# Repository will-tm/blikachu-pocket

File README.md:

<div align="center">

# BLikachu Pocket

**A Game Boy, NES and SNES handheld inside a Pocket Pikachu: a replacement BL618 board and Zephyr firmware for the
Nintendo MPG-001 shell.**

**[Hardware](#hardware) · [Build and flash](#build-and-flash) · [Add games](#add-games) · [Controls](#controls) · [Firmware docs](firmware/README.md)**

</div>

## New insides, same shell

- **Three systems:** GB and GBC (Gambatte), NES (FCEUmm) and SNES (Snes9x2005), picked from the ROM's header and
  extension.
- **Saves:** save states, cartridge battery RAM and RTC data, kept across firmware updates.
- **Wi-Fi:** a web UI to upload and delete ROMs, play remotely and update the firmware over the air.
- **USB:** DFU firmware updates, a shell, and ROM and save uploads without Wi-Fi.

## How it works

<p align="center">
  <picture>
    <source media="(prefers-color-scheme: dark)" srcset="assets/overview-dark.svg">
    <img alt="Inside the shell, a BL618 running Zephyr at 480 MHz loads one libretro core at a time: Gambatte for GB and GBC, FCEUmm for NES or Snes9x2005 for SNES. Its 4 MiB of PSRAM is split into 512 KiB of buffers and a 3.5 MiB core and update workspace. The buttons, IMU and power circuit feed it; it drives the ST7789V LCD and the buzzer. A 64 MiB quad SPI flash holds 8 MiB of firmware, an 8 MiB LittleFS volume for settings, saves and the ROM catalogue, and 48 MiB of contiguous, memory-mapped ROMs. A browser reaches the web UI over Wi-Fi, and a computer connects over high-speed USB." src="assets/overview-light.svg">
  </picture>
</p>

## Hardware

| Part    | Detail                                                             |
| ------- | ------------------------------------------------------------------ |
| SoC     | Bouffalo Lab BL618 RISC-V, 4 MiB PSRAM, CPU overclocked to 480 MHz |
| Flash   | W25Q512JV, 64 MiB QSPI                                             |
| Display | ST7789V SPI colour LCD, 240×216 visible                            |
| Input   | D-pad and four buttons                                             |
| Sound   | PWM buzzer                                                         |
| Motion  | LSM6DSV16X IMU                                                     |
| Power   | MCP73871 Li-ion charger, battery measurement, GPIO power latch     |
| Radio   | Wi-Fi                                                              |
| USB     | High speed: CDC shell and DFU                                      |

Open [the KiCad project](hardware/blikachu-pocket.kicad_pro) in KiCad 10.

## Build and flash

You need Python 3, CMake, Ninja, [Zephyr SDK](https://github.com/zephyrproject-rtos/sdk-ng/releases) 1.0.1 with the
RISC-V toolchain, and `dfu-util`. On macOS:

```sh
brew install cmake ninja dtc dfu-util
cd firmware
./build.sh
```

**First flash:** hold BOOT while resetting, release it, then pass the serial port that appears:

```sh
FLASH_PORT=/dev/cu.usbmodemXXXXX ./build.sh flash
```

**Updates:** with the firmware running, no buttons needed:

```sh
./build.sh flash
```

Keep power connected until the board reboots: `Download done` means the transfer has finished, not the installation.

### Recovery

An interrupted or broken install is recovered the same way as the first flash: BOOT, reset, then `./build.sh flash`
with `FLASH_PORT`. Details: [firmware documentation](firmware/README.md#firmware-updates).

## Add games

Upload your own `.gb`, `.gbc`, `.nes`, `.sfc` or `.smc` files.

**Over Wi-Fi:** add a network from the USB shell, then open the board's IP address in a browser:

```text
wifi_cred add <ssid> <passphrase>
wifi_cred connect
```

**Over USB:** from the `firmware` directory. This also sends libretro save files.

```sh
source .venv/bin/activate
python tools/usb_upload.py --port /dev/cu.usbmodemXXXXX game.gbc
```

SNES support covers ordinary LoROM and HiROM cartridges; enhancement-chip games are rejected.

## Controls

| Buttons               | Action            |
| --------------------- | ----------------- |
| SELECT + START        | Quit to the menu  |
| SELECT + B            | Save state        |
| SELECT + A            | Restore state     |
| SELECT + UP / DOWN    | Volume            |
| SELECT + LEFT / RIGHT | Brightness        |
| Hold START            | Request power-off |

On SNES, A and B act as B and Y, SELECT + A / B as A and X, and SELECT + LEFT / RIGHT as L and R. Save states and
brightness move to the shell. Remote play exposes all twelve SNES buttons.

## Development

- [Firmware documentation](firmware/README.md): cores, storage, updates and the shell.
- [Firmware development notes](firmware/CLAUDE.md): pin assignments, scheduling and memory constraints, Zephyr
  patches.

GitHub Actions builds the firmware and renders the PCB in 3D on hardware changes. The render above is refreshed on
pushes to `main`; pull requests get a preview artifact.

## Disclaimers

BLikachu Pocket is provided **as is, without any warranty**: you modify your device at your own risk.

- It is an independent hardware and firmware project, not affiliated with or endorsed by Nintendo. Nintendo, Game Boy,
  Pokémon and Pikachu are trademarks of their respective owners.
- No games are included.
- The emulator cores keep their own licenses, in their dependency repositories. Snes9x's license includes
  non-commercial distribution restrictions.

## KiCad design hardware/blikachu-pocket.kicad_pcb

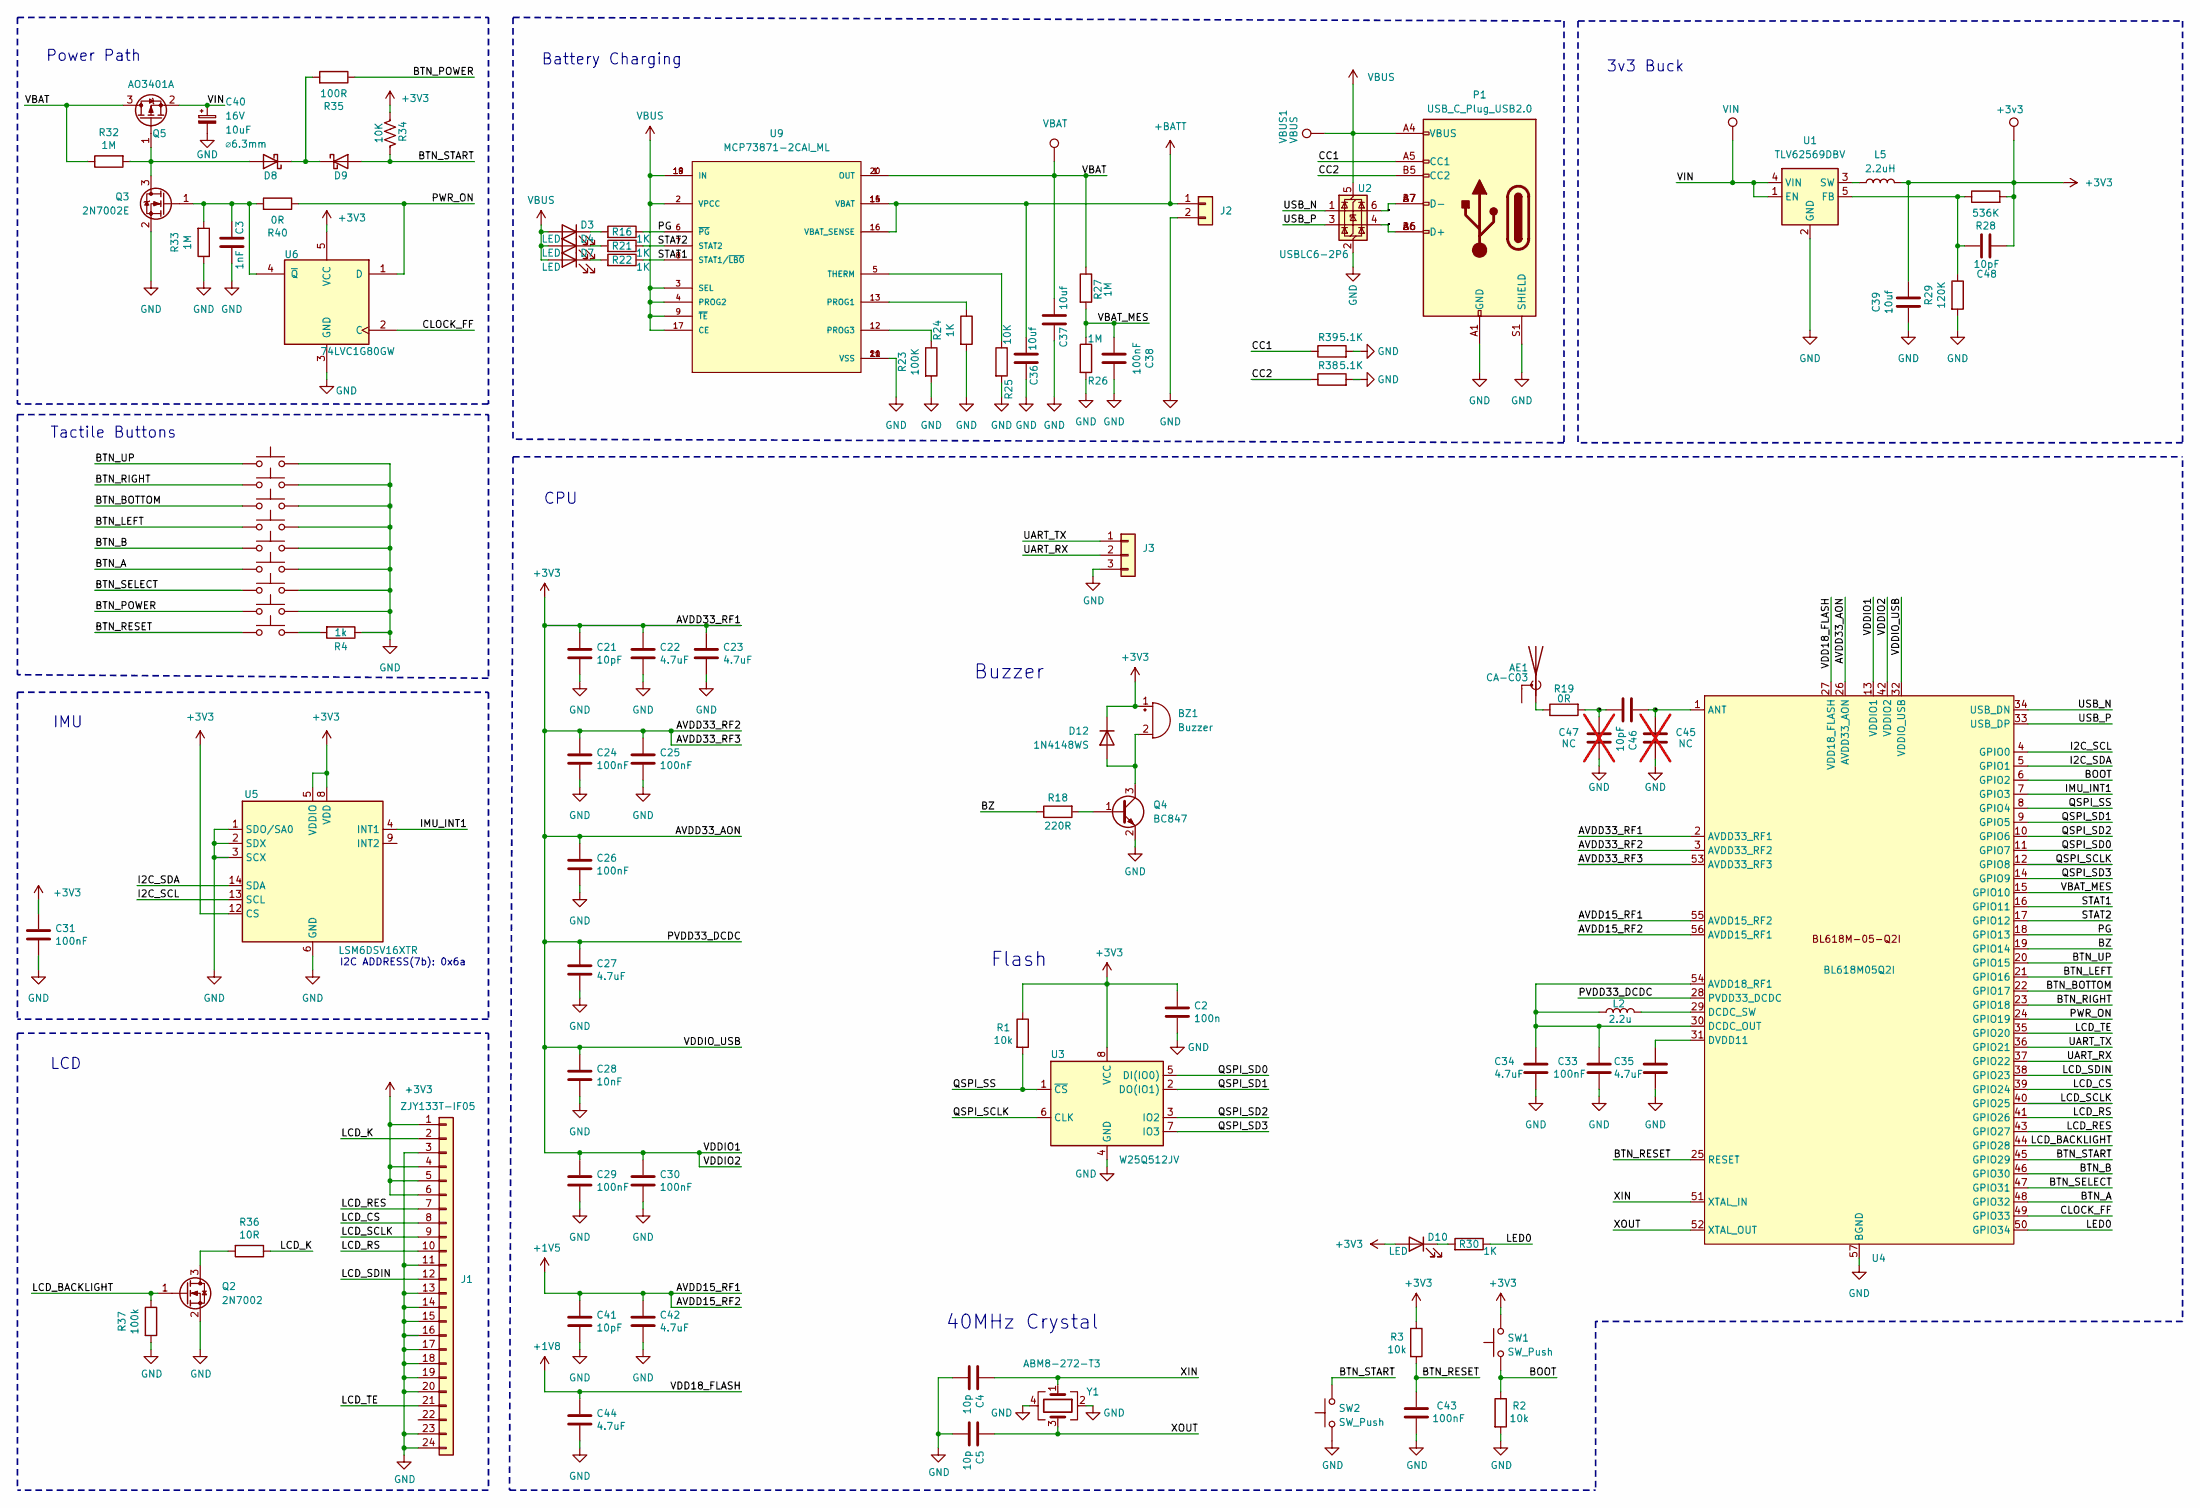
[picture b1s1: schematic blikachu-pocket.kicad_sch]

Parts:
+3v3: +3v3; TestPoint_Pad_D1.0mm
A0: ESPKACHU-PAD
AE1: CA-C03
B0: ESPKACHU-PAD
BZ1: Buzzer; CUI_CSS-0575A-SMT
C2: 100n; C_0402_1005Metric
C3: 1nF; C_0402_1005Metric
C4, C5: 10p; C_0402_1005Metric
C21, C41, C46, C48: 10pF; C_0402_1005Metric
C22, C23, C27, C34, C35, C42, C44: 4.7uF; C_0402_1005Metric
C24, C25, C26, C29, C30, C31, C33, C38, C43: 100nF; C_0402_1005Metric
C28: 10nF; C_0402_1005Metric
C36, C37: 10uf; C_0805_2012Metric
C39: 10uf; C_1206_3216Metric_Pad1.33x1.80mm_HandSolder
C40: 865080443007; C_1206_3216Metric_Pad1.33x1.80mm_HandSolder; Voltage 16V; Part Number 865080443007
C45, C47: NC; C_0402_1005Metric; not fitted
D3, D4, D7, D10: LED; LED_0603_1608Metric
D8, D9: D_Schottky; D_0603_1608Metric_Pad1.05x0.95mm_HandSolder
D12: 1N4148WS; D_SOD-323_HandSoldering
DOWN0: ESPKACHU-PAD
J1: ZJY133T-IF05; Hirose_FH12-24S-0.5SH_1x24-1MP_P0.50mm_Horizontal
J2: Conn_01x02; PinHeader_1x02_P2.00mm_Vertical
J3: Conn_01x03; PinHeader_1x03_P2.00mm_Vertical
L2: 2.2u; L_pol_2016
L5: 2.2uH; L_Changjiang_FTC201607S
LEFT0: ESPKACHU-PAD
P1: USB_C_Plug_USB2.0; USB_C_Receptacle_GCT_USB4105-xx-A_16P_TopMnt_Horizontal
Q2: 2N7002; SOT-23
Q3: 2N7002E; SOT-23
Q4: BC847; SOT-23
Q5: AO3401A; SOT-23
R1, R2, R3: 10k; R_0402_1005Metric
R4: 1k; R_0402_1005Metric
R16, R21, R22, R24, R30: 1K; R_0402_1005Metric
R18: 220R; R_0402_1005Metric
R19, R40: 0R; R_0402_1005Metric
R23: 100K; R_0402_1005Metric
R25: 10K; R_0402_1005Metric
R26, R27, R32, R33: 1M; R_0402_1005Metric
R28: 536K; R_0402_1005Metric
R29: 120K; R_0402_1005Metric
R34: 10K; R_0402_1005Metric; Tolerance 1%
R35: 100R; R_0402_1005Metric
R36: 10R; R_0805_2012Metric
R37: 100k; R_0402_1005Metric
R38, R39: 5.1K; R_0402_1005Metric; MPN RC0603FR-072K2L; Digi-Key_PN 311-2.20KHRCT-ND
RIGHT0: ESPKACHU-PAD
SELECT0: ESPKACHU-PAD
START0, START1: ESPKACHU-PAD
SW1, SW2: SW_Push; TS-A001A
U1: TLV62569DBV; SOT-23-5
U2: USBLC6-2P6; SOT-666
U3: W25Q512JV; SOIC-8_5.3x6.2mm_P1.27mm
U4: BL618M05Q2I; QFN-56_EP_7x7_Pitch0.4mm
U5: LSM6DSV16XTR; LGA-14_3x2.5mm_P0.5mm_LayoutBorder3x4y
U6: 74LVC1G80GW; SOT-353_SC-70-5
U9: MCP73871-2CAI_ML; QFN-20-1EP_4x4mm_P0.5mm_EP2.5x2.5mm_ThermalVias; PARTREV D
UP0: ESPKACHU-PAD
VBAT1: VBAT; TestPoint_Pad_D1.0mm
VBUS1: VBUS; TestPoint_Pad_D1.0mm
VIN1: VIN; TestPoint_Pad_D1.0mm
Y1: ABM8-272-T3; Crystal_SMD_3225-4Pin_3.2x2.5mm

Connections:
+1V5: C41.1, C42.1, U4.55 (AVDD15_RF2), U4.56 (AVDD15_RF1)
+1V8: C44.1, U4.27 (VDD18_FLASH)
+3V3: +3v3.1 (1_1), BZ1.1 (-), C2.1, C21.1, C22.1, C23.1, C24.1, C25.1, C26.1, C27.1, C28.1, C29.1, C30.1, C31.1, C39.2, C48.1, D10.2 (A), D12.2 (K), J1.1, J1.4, J1.5, J1.6, L5.2, R1.1, R3.1, R28.2, R34.2, SW1.2, U3.8 (VCC), U4.2 (AVDD33_RF1), U4.3 (AVDD33_RF2), U4.13 (VDDIO1), U4.26 (AVDD33_AON), U4.28 (PVDD33_DCDC), U4.32 (VDDIO_USB), U4.42 (VDDIO2), U4.53 (AVDD33_RF3), U5.5 (VDDIO), U5.8 (VDD), U5.12 (CS), U6.5 (VCC)
+BATT: C36.2, J2.1, U9.14 (VBAT), U9.15 (VBAT), U9.16 (VBAT_SENSE)
/ANT_PATH1: C45.1, C46.1, U4.1 (ANT)
/ANT_PATH2: C46.2, C47.1, R19.2
/BOOT: R2.1, SW1.1, U4.6 (GPIO2)
/BTN_A: A0.1, U4.48 (GPIO32)
/BTN_B: B0.1, U4.46 (GPIO30)
/BTN_BOTTOM: DOWN0.1, U4.22 (GPIO17)
/BTN_LEFT: LEFT0.1, U4.21 (GPIO16)
/BTN_POWER: R35.1, START0.1
/BTN_RESET: C43.1, R3.2, START1.1, U4.25 (RESET)
/BTN_RIGHT: RIGHT0.1, U4.23 (GPIO18)
/BTN_SELECT: SELECT0.1, U4.47 (GPIO31)
/BTN_START: D9.2 (A), R34.1, SW2.2, U4.45 (GPIO29)
/BTN_UP: U4.20 (GPIO15), UP0.1
/BZ: R18.1, U4.19 (GPIO14)
/CC1: P1.A5 (CC1), R39.1
/CC2: P1.B5 (CC2), R38.1
/CLOCK_FF: U4.49 (GPIO33), U6.2 (C)
/I2C_SCL: U4.4 (GPIO0), U5.13 (SCL)
/I2C_SDA: U4.5 (GPIO1), U5.14 (SDA)
/IMU_INT1: U4.7 (GPIO3), U5.4 (INT1)
/LCD_BACKLIGHT: Q2.1 (G), R37.1, U4.44 (GPIO28)
/LCD_CS: J1.8, U4.39 (GPIO24)
/LCD_K: J1.2, R36.1
/LCD_RES: J1.7, U4.43 (GPIO27)
/LCD_RS: J1.10, U4.41 (GPIO26)
/LCD_SCLK: J1.9, U4.40 (GPIO25)
/LCD_SDIN: J1.12, U4.38 (GPIO23)
/LCD_TE: J1.21, U4.35 (GPIO20)
/LED0: R30.1, U4.50 (GPIO34)
/PG: R16.1, U4.18 (GPIO13), U9.6 (~PG)
/PWR_ON: R40.1, U4.24 (GPIO19), U6.1 (D)
/QSPI_SCLK: U3.6 (CLK), U4.12 (GPIO8)
/QSPI_SD0: U3.5 (DI(IO0)), U4.11 (GPIO7)
/QSPI_SD1: U3.2 (DO(IO1)), U4.9 (GPIO5)
/QSPI_SD2: U3.3 (IO2), U4.10 (GPIO6)
/QSPI_SD3: U3.7 (IO3), U4.14 (GPIO9)
/QSPI_SS: R1.2, U3.1 (~CS), U4.8 (GPIO4)
/STAT1: R22.1, U4.16 (GPIO11), U9.8 (STAT1/~LBO)
/STAT2: R21.1, U4.17 (GPIO12), U9.7 (STAT2)
/UART_RX: J3.2, U4.37 (GPIO22)
/UART_TX: J3.1, U4.36 (GPIO21)
/USB_CON_N: P1.A7 (D-), P1.B7 (D-), U2.6 (I/O1)
/USB_CON_P: P1.A6 (D+), P1.B6 (D+), U2.4 (I/O2)
/USB_N: U2.1 (I/O1), U4.34 (USB_DN)
/USB_P: U2.3 (I/O2), U4.33 (USB_DP)
/VBAT: C37.2, Q5.3 (D), R27.1, R32.1, U9.1 (OUT), U9.20 (OUT), VBAT1.1 (1_1)
/VBAT_MES: C38.2, R26.1, R27.2, U4.15 (GPIO10)
/VIN: C40.1, Q5.2 (S), U1.1 (EN), U1.4 (VIN), VIN1.1 (1_1)
/XIN: C4.1, U4.51 (XTAL_IN), Y1.1
/XOUT: C5.1, U4.52 (XTAL_OUT), Y1.3
GND: A0.2, B0.2, C2.2, C3.1, C4.2, C5.2, C21.2, C22.2, C23.2, C24.2, C25.2, C26.2, C27.2, C28.2, C29.2, C30.2, C31.2, C33.2, C34.2, C35.2, C36.1, C37.1, C38.1, C39.1, C40.2, C41.2, C42.2, C43.2, C44.2, C45.2, C47.2, DOWN0.2, J1.3, J1.11, J1.13, J1.14, J1.15, J1.16, J1.17, J1.18, J1.19, J1.20, J1.23, J1.24, J2.2, J3.3, LEFT0.2, P1.A1 (GND), P1.A12 (GND), P1.B1 (GND), P1.B12 (GND), P1.S1 (SHIELD), Q2.2 (S), Q3.2 (S), Q4.2 (E), R2.2, R4.1, R23.2, R24.2, R25.2, R26.2, R29.2, R33.1, R37.2, R38.2, R39.2, RIGHT0.2, SELECT0.2, START0.2, SW2.1, U1.2 (GND), U2.2 (GND), U3.4 (GND), U4.57 (BGND), U5.1 (SDO/SA0), U5.2 (SDX), U5.3 (SCX), U5.6 (GND), U5.7 (GND), U6.3 (GND), U9.10 (VSS), U9.11 (VSS), U9.21 (VSS), UP0.2, Y1.2, Y1.4
unnamed: AE1.1 (A_1), R19.1
unnamed: BZ1.2 (+), D12.1 (A), Q4.3 (C)
unnamed: D3.1 (K), R16.2
unnamed: D4.1 (K), R21.2
unnamed: D7.1 (K), R22.2
unnamed: D8.2 (A), Q3.3 (D), Q5.1 (G), R32.2
unnamed: D8.1 (K), D9.1 (K), R35.2
unnamed: D10.1 (K), R30.2
unnamed: Q2.3 (D), R36.2
unnamed: C3.2, Q3.1 (G), R33.2, R40.2, U6.4 (~Q)
unnamed: Q4.1 (B), R18.2
unnamed: R4.2, START1.2
unnamed: C48.2, R28.1, R29.1, U1.5 (FB)
unnamed: L5.1, U1.3 (SW)
unnamed: C33.1, C34.1, L2.1, U4.30 (DCDC_OUT), U4.54 (AVDD18_RF1)
unnamed: L2.2, U4.29 (DCDC_SW)
unnamed: C35.1, U4.31 (DVDD11)
unnamed: R24.1, U9.13 (PROG1)
unnamed: R23.1, U9.12 (PROG3)
unnamed: R25.1, U9.5 (THERM)
VBUS: D3.2 (A), D4.2 (A), D7.2 (A), P1.A4 (VBUS), P1.A9 (VBUS), P1.B4 (VBUS), P1.B9 (VBUS), U2.5 (VBUS), U9.2 (VPCC), U9.3 (SEL), U9.4 (PROG2), U9.9 (~TE), U9.17 (CE), U9.18 (IN), U9.19 (IN), VBUS1.1 (1_1)

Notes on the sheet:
Tactile Buttons
Battery Charging
3v3 Buck
LCD
Power Path
CPU
I2C ADDRESS(7b): 0x6a
40MHz Crystal
Buzzer
Flash
IMU

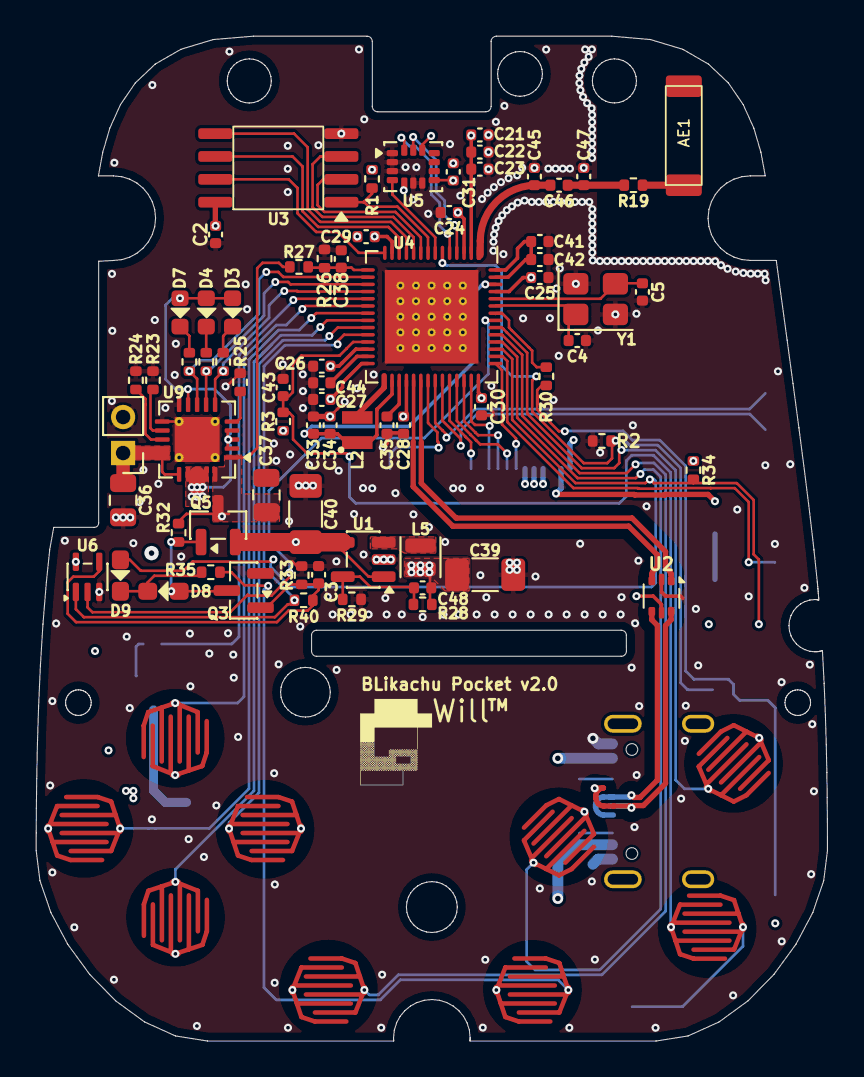
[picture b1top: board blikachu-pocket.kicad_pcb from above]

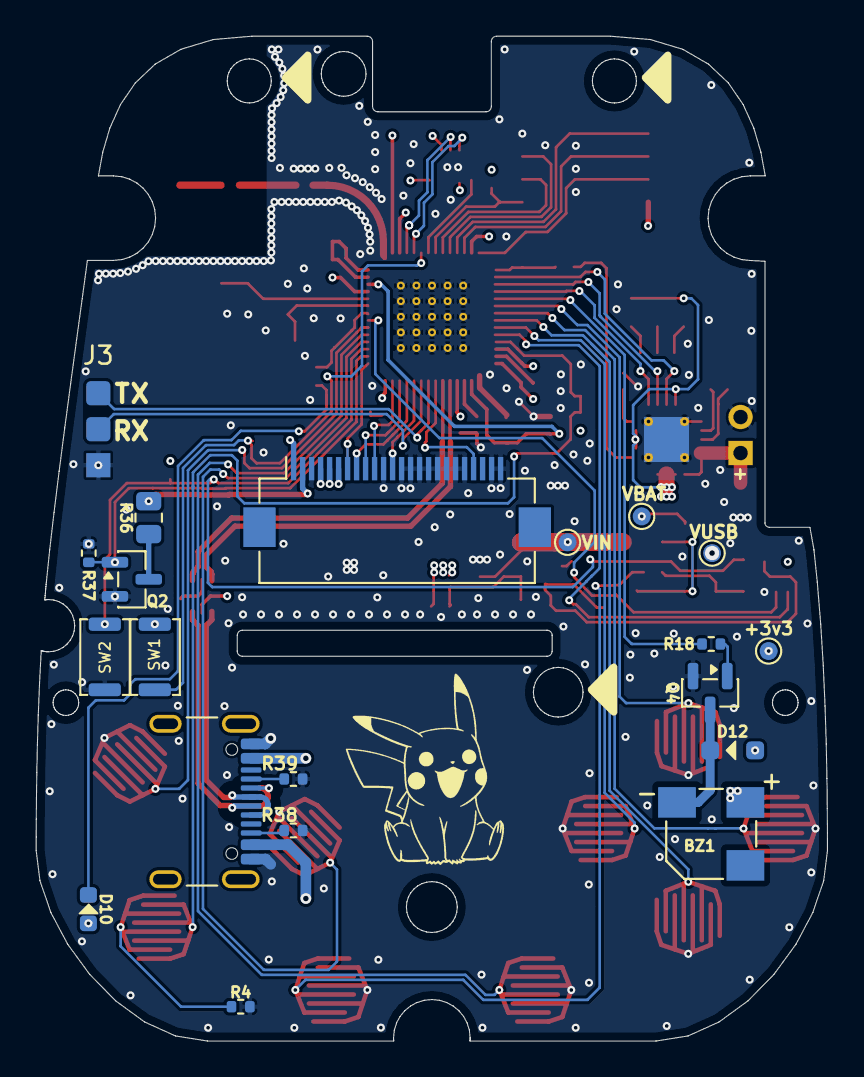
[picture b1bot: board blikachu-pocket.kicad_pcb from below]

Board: 4 copper layers, 44.0 x 55.8 mm, 99 parts (20 on the bottom side), 76 nets.

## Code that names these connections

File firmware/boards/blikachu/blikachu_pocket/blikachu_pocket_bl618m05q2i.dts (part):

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 *
 * Pin map (from hardware/ PCB netlist — pads are ground truth,
 * the schematic is partly an Eagle import):
 *   I2C0 (LSM6DSV16X IMU, INT1=GPIO3):
 *     SCL=GPIO0  SDA=GPIO1
 *   BOOT button (SW1, to +3V3 — BootROM entry, not an input key):
 *     GPIO2
 *   QSPI flash on SF2 pad set (external — BL618M05 has no internal
 *   die): W25Q512JV 64 MB (U3).
 *     CS=GPIO4 D1=GPIO5 D2=GPIO6 D0=GPIO7 CLK=GPIO8 D3=GPIO9
 *   Battery measurement: VBAT_MES=GPIO10 (VBAT/2, ADC CH7)
 *   Charger status (MCP73871, open-drain active-low):
 *     STAT1=GPIO11  STAT2=GPIO12  PG=GPIO13
 *   Magnetic buzzer (BZ1 on +3V3 via Q4 BC847, D12 flyback):
 *     GPIO14 (PWM0 CH2P)
 *   D-pad / buttons (active-low, internal pull-up):
 *     UP=GPIO15  LEFT=GPIO16  DOWN=GPIO17  RIGHT=GPIO18
 *     START=GPIO29  B=GPIO30  SELECT=GPIO31  A=GPIO32
 *   Power latch (74LVC1G80 ~Q -> Q3 NMOS -> Q5 PMOS, VBAT->VIN):
 *     D=GPIO19 (/PWR_ON)  CP=GPIO33 (/CLOCK_FF)
 *     R40 (0R) ties D to ~Q: a toggle flip-flop, each CP rising edge
 *     flips power. ~Q high = held. GPIO19 is input-only (reads ~Q).
 *     Power button pulls Q5's gate via D8 (and reads as START via D9).
 *   ST7789V SPI 240x240 (ZJY133T-IF05 FPC, write-only):
 *     MOSI=GPIO23  CS=GPIO24  SCLK=GPIO25  DC(RS)=GPIO26  RST=GPIO27
 *     TE=GPIO20  Backlight=GPIO28 (Q2 low-side, PWM0 CH0P)
 *   UART0 console/shell (J3 header + CKLink adapter):
 *     TX=GPIO21  RX=GPIO22  (BootROM download pins too)
 *   USB-C: native USB HS PHY (dedicated pins, via USBLC6 ESD) —
 *     CDC ACM shell via the bl61x UDC (patches/0003).
 *   LED0=GPIO34
 *
 * GPIO numbering: gpio0 covers GPIO0-31, gpio1 covers GPIO32-34
 * (pins 0-2).
 *
 * Flash layout (64 MB W25Q512JV, 4-byte addresses):
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
	zephyr,user {
		/* ST7789V tear-effect output. */
		te-gpios = <&gpio0 20 GPIO_ACTIVE_HIGH>;
		/* Backlight moved off PWM0 (single global period shared
		 * with the buzzer — every note retuned it): timer0
		 * soft-PWM drives the pin as plain GPIO instead.
		 */
		backlight-gpios = <&gpio0 28 GPIO_ACTIVE_HIGH>;

		/* MCP73871 status outputs (open-drain, LED-loaded — internal
		 * pull-ups required for a solid released level).
		 */
		chg-stat1-gpios = <&gpio0 11 (GPIO_ACTIVE_LOW | GPIO_PULL_UP)>;
		chg-stat2-gpios = <&gpio0 12 (GPIO_ACTIVE_LOW | GPIO_PULL_UP)>;
		chg-pg-gpios = <&gpio0 13 (GPIO_ACTIVE_LOW | GPIO_PULL_UP)>;

		/* 74LVC1G80 power latch, D tied to ~Q (R40): GPIO19 reads
		 * the state (high = held), a CP rising edge toggles it.
		 */
		pwr-d-gpios = <&gpio0 19 GPIO_ACTIVE_HIGH>;
		pwr-clk-gpios = <&gpio1 1 GPIO_ACTIVE_HIGH>;	/* GPIO33 */
	};

	keys: gpio_keys {
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		polling-mode;

		key_up: key_up {
			gpios = <&gpio0 15 (GPIO_ACTIVE_LOW | GPIO_PULL_UP)>;
			zephyr,code = <INPUT_KEY_UP>;
		};
		key_down: key_down {
			gpios = <&gpio0 17 (GPIO_ACTIVE_LOW | GPIO_PULL_UP)>;
			zephyr,code = <INPUT_KEY_DOWN>;
		};
		key_left: key_left {
			gpios = <&gpio0 16 (GPIO_ACTIVE_LOW | GPIO_PULL_UP)>;
			zephyr,code = <INPUT_KEY_LEFT>;
		};
		key_right: key_right {
			gpios = <&gpio0 18 (GPIO_ACTIVE_LOW | GPIO_PULL_UP)>;
			zephyr,code = <INPUT_KEY_RIGHT>;
		};
		key_a: key_a {
			gpios = <&gpio1 0 (GPIO_ACTIVE_LOW | GPIO_PULL_UP)>;	/* GPIO32 */
			zephyr,code = <INPUT_BTN_A>;
		};
		key_b: key_b {
			gpios = <&gpio0 30 (GPIO_ACTIVE_LOW | GPIO_PULL_UP)>;
			zephyr,code = <INPUT_BTN_B>;
		};
		key_start: key_start {
			gpios = <&gpio0 29 (GPIO_ACTIVE_LOW | GPIO_PULL_UP)>;
			zephyr,code = <INPUT_BTN_START>;
		};
		key_select: key_select {
			gpios = <&gpio0 31 (GPIO_ACTIVE_LOW | GPIO_PULL_UP)>;
			zephyr,code = <INPUT_BTN_SELECT>;
		};
	};
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	leds {
		compatible = "gpio-leds";
		led_0: led_0 {
			gpios = <&gpio1 2 GPIO_ACTIVE_LOW>;	/* GPIO34 */
			label = "LED0";
		};
	};

	mipi_dbi {
		compatible = "zephyr,mipi-dbi-spi";
		spi-dev = <&spi0>;
		dc-gpios = <&gpio0 26 GPIO_ACTIVE_HIGH>;
		reset-gpios = <&gpio0 27 GPIO_ACTIVE_LOW>;
		write-only;
		#address-cells = <1>;
		#size-cells = <0>;
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	pwmleds {
		compatible = "pwm-leds";
		pwm_buzzer: pwm_buzzer {
			pwms = <&pwm0 2 0 PWM_POLARITY_NORMAL>;	/* GPIO14 CH2P */
		};
	};
};
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
	adc0_default: adc0_default {
		group1 {
			pinmux = <GPIO10_ADC_CH7>;	/* VBAT_MES = VBAT/2 */
		};
	};

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	lsm6dsv16x: lsm6dsv16x@6a {
		compatible = "st,lsm6dsv16x";
		reg = <0x6a>;
		int1-gpios = <&gpio0 3 GPIO_ACTIVE_HIGH>;
		accel-odr = <LSM6DSVXXX_DT_ODR_AT_60Hz>;
		accel-range = <LSM6DSV16X_DT_FS_2G>;
		status = "okay";
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	pinctrl-0 = <&spi0_display>;
	pinctrl-names = "default";

	cs-gpios = <&gpio0 24 GPIO_ACTIVE_LOW>;

	/* Display push: TX over DMA channel 0 (trigsrc 0xb = SPI0_TX) */
	dmas = <&dma0 0 0xb>;
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	status = "okay";
};

&gpio0 {
	status = "okay";
};

&gpio1 {
	status = "okay";
};

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

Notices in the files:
firmware/boards/blikachu/blikachu_pocket/blikachu_pocket_bl618m05q2i.dts:
SPDX-License-Identifier: Apache-2.0
